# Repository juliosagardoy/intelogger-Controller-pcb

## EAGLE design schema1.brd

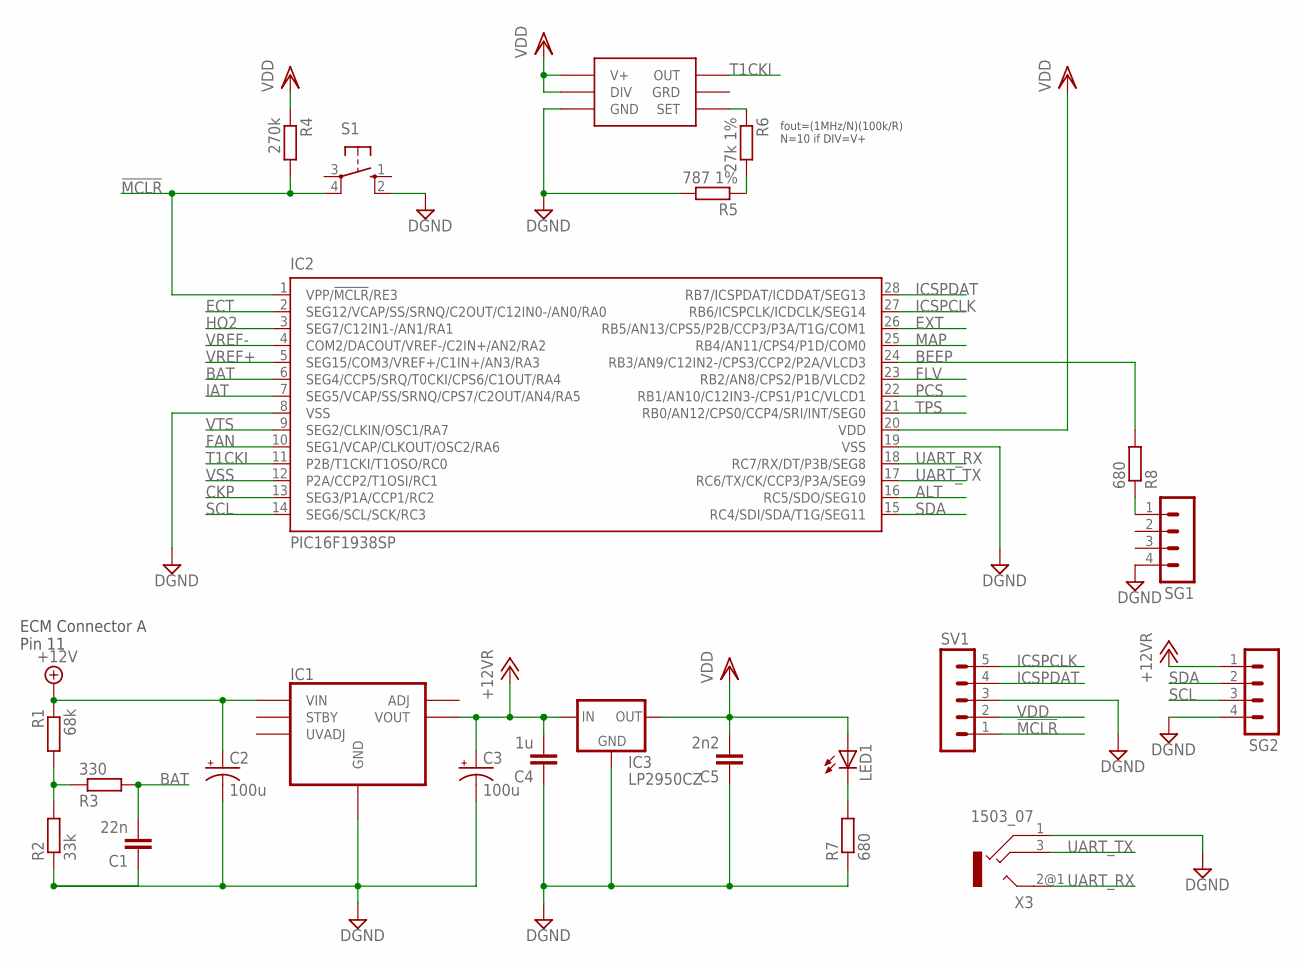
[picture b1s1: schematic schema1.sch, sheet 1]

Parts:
C1: 22n; C5B3
C2, C3: 100u; E5-10,5
C4: 1u; C5B2.5
C5: 2n2; C5B2.5
IC1: EXCALIBURPKG1360; TI_PKG1360
IC2: PIC16F1938SP; DIL28-3
IC3: LP2950CZ; TO92
IC4: LTC6906; TSOT23-6
LED1: LEDCHIP-LED0805; CHIP-LED0805
R1: 68k; M1206
R2: 33k; M1206
R3: 330; M1206
R4: 270k; M1206
R5: 787 1%; M0805
R6: 27k 1%; M0805
R7, R8: 680; M1206
S1: 10-XX; B3F-10XX
SG1, SG2: MA04-1
SV1: MA05-1
X3: 1503_07

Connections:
!MCLR: IC2.1 (VPP/!MCLR!/RE3), R4.2, S1.4 (P1), SV1.1
+12V: C2.+, IC1.P$4 (VIN), IC1.P$5 (VIN), IC1.P$6 (VIN), R1.1; also elsewhere on the board
+12VR: C3.+, C4.2, IC1.P$11 (VOUT), IC1.P$12 (VOUT), IC1.P$13 (VOUT), IC3.3 (IN), SG2.1
ALT: IC2.16 (RC5/SDO/SEG10); also elsewhere on the board
BAT: C1.2, IC2.6 (SEG4/CCP5/SRQ/T0CKI/CPS6/C1OUT/RA4), R3.2
BEEP: IC2.24 (RB3/AN9/C12IN2-/CPS3/CCP2/P2A/VLCD3), R8.2
CKP: IC2.13 (SEG3/P1A/CCP1/RC2); also elsewhere on the board
DGND: C1.1, C2.-, C3.-, C4.1, C5.1, IC1.P$7 (GND), IC1.P$8 (GND), IC1.P$9 (GND), IC1.P$10 (GND), IC2.8 (VSS), IC2.19 (VSS), IC3.2 (GND), IC4.2 (GND), R2.1, R5.2, R7.1, S1.2 (S1), SG1.4, SG2.4, SV1.3, X3.1; also elsewhere on the board
ECT: IC2.2 (SEG12/VCAP/SS/SRNQ/C2OUT/C12IN0-/AN0/RA0); also elsewhere on the board
EXT: IC2.26 (RB5/AN13/CPS5/P2B/CCP3/P3A/T1G/COM1); also elsewhere on the board
FAN: IC2.10 (SEG1/VCAP/CLKOUT/OSC2/RA6); also elsewhere on the board
FLV: IC2.23 (RB2/AN8/CPS2/P1B/VLCD2); also elsewhere on the board
HO2: IC2.3 (SEG7/C12IN1-/AN1/RA1); also elsewhere on the board
IAT: IC2.7 (SEG5/VCAP/SS/SRNQ/CPS7/C2OUT/AN4/RA5); also elsewhere on the board
ICSPCLK: IC2.27 (RB6/ICSPCLK/ICDCLK/SEG14), SV1.5
ICSPDAT: IC2.28 (RB7/ICSPDAT/ICDDAT/SEG13), SV1.4
MAP: IC2.25 (RB4/AN11/CPS4/P1D/COM0); also elsewhere on the board
unnamed: R8.1, SG1.1
unnamed: IC4.4 (SET), R6.1
unnamed: LED1.C, R7.2
unnamed: R5.1, R6.2
unnamed: R1.2, R2.2, R3.1
PCS: IC2.22 (RB1/AN10/C12IN3-/CPS1/P1C/VLCD1); also elsewhere on the board
SCL: IC2.14 (SEG6/SCL/SCK/RC3), SG2.3
SDA: IC2.15 (RC4/SDI/SDA/T1G/SEG11), SG2.2
T1CKI: IC2.11 (P2B/T1CKI/T1OSO/RC0), IC4.1 (OUT)
TPS: IC2.21 (RB0/AN12/CPS0/CCP4/SRI/INT/SEG0); also elsewhere on the board
UART_RX: IC2.18 (RC7/RX/DT/P3B/SEG8), X3.2@1 (2)
UART_TX: IC2.17 (RC6/TX/CK/CCP3/P3A/SEG9), X3.3
VDD: C5.2, IC2.20 (VDD), IC3.1 (OUT), IC4.3 (DIV), IC4.6 (V+), LED1.A, R4.1, SV1.2
VREF+: IC2.5 (SEG15/COM3/VREF+/C1IN+/AN3/RA3); also elsewhere on the board
VREF-: IC2.4 (COM2/DACOUT/VREF-/C2IN+/AN2/RA2); also elsewhere on the board
VSS: IC2.12 (P2A/CCP2/T1OSI/RC1); also elsewhere on the board
VTS: IC2.9 (SEG2/CLKIN/OSC1/RA7); also elsewhere on the board

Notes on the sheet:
ECM Connector A Pin 11
fout=(1MHz/N)(100k/R) N=10 if DIV=V+

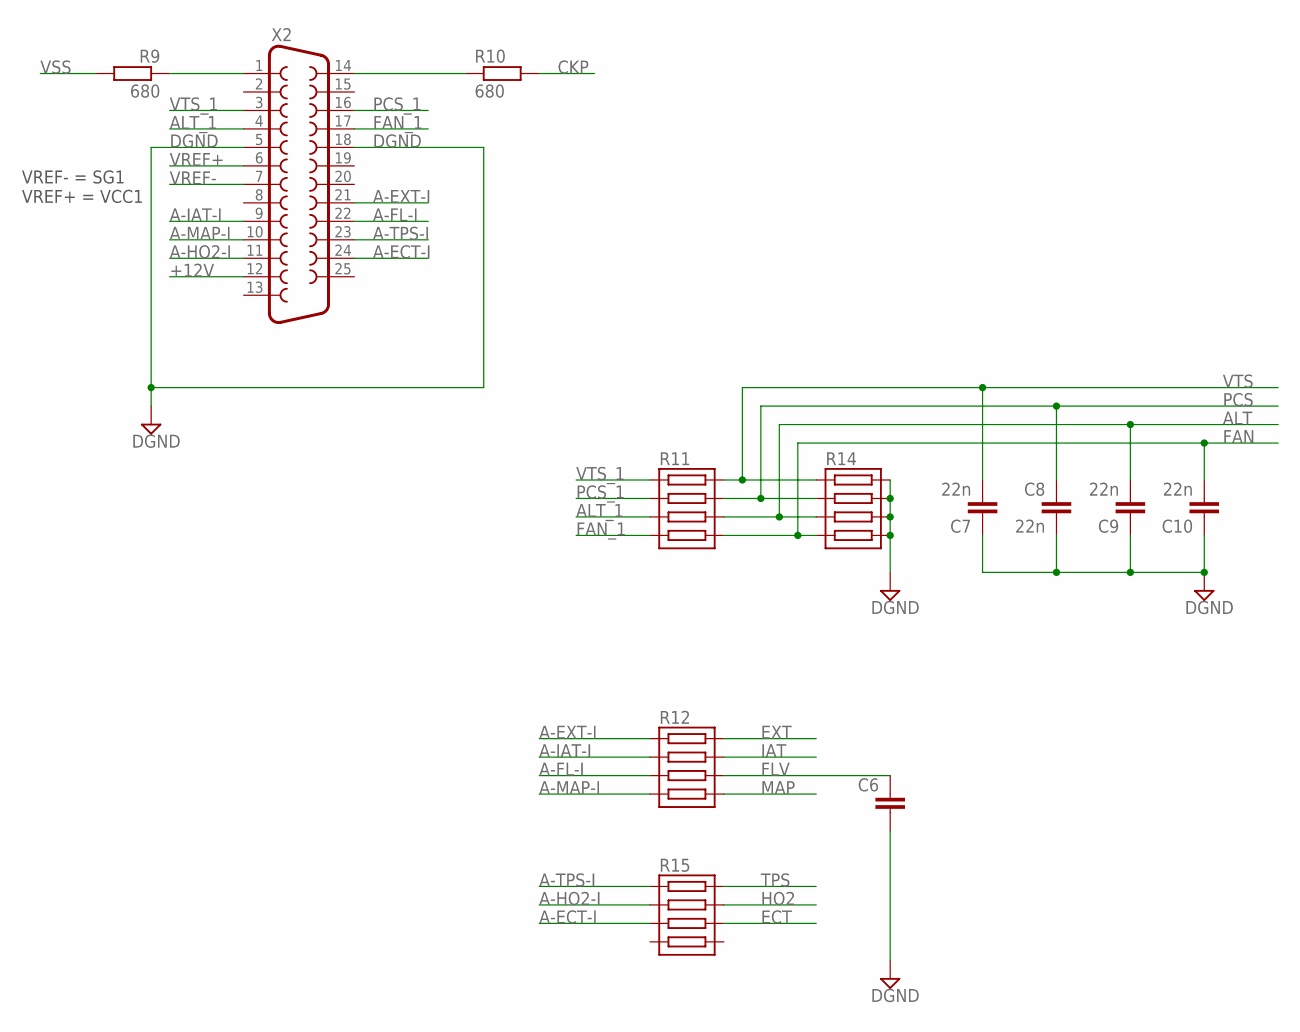
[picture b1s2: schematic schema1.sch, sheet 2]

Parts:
C6: C5/3; C5B3
C7, C8, C9, C10: 22n; C5B3
R9, R10: 680; M1206
R11, R12, R14, R15: RESISTOR_ARRAY; RES_ARRAY_DIP_4
X2: F25H

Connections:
+12V: X2.12; also elsewhere on the board
A-ECT-I: R15.P$5, X2.24
A-EXT-I: R12.P$1, X2.21
A-FL-I: R12.P$5, X2.22
A-HO2-I: R15.P$3, X2.11
A-IAT-I: R12.P$3, X2.9
A-MAP-I: R12.P$7, X2.10
A-TPS-I: R15.P$1, X2.23
ALT: C9.2, R11.P$6, R14.P$5; also elsewhere on the board
ALT_1: R11.P$5, X2.4
CKP: R10.2; also elsewhere on the board
DGND: C6.2, C7.1, C8.2, C9.1, C10.1, R14.P$2, R14.P$4, R14.P$6, R14.P$8, X2.5, X2.18; also elsewhere on the board
ECT: R15.P$6; also elsewhere on the board
EXT: R12.P$2; also elsewhere on the board
FAN: C10.2, R11.P$8, R14.P$7; also elsewhere on the board
FAN_1: R11.P$7, X2.17
FLV: C6.1, R12.P$6; also elsewhere on the board
HO2: R15.P$4; also elsewhere on the board
IAT: R12.P$4; also elsewhere on the board
MAP: R12.P$8; also elsewhere on the board
unnamed: R9.1, X2.1
unnamed: R10.1, X2.14
PCS: C8.1, R11.P$4, R14.P$3; also elsewhere on the board
PCS_1: R11.P$3, X2.16
TPS: R15.P$2; also elsewhere on the board
VREF+: X2.6; also elsewhere on the board
VREF-: X2.7; also elsewhere on the board
VSS: R9.2; also elsewhere on the board
VTS: C7.2, R11.P$2, R14.P$1; also elsewhere on the board
VTS_1: R11.P$1, X2.3

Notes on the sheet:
VREF- = SG1 VREF+ = VCC1

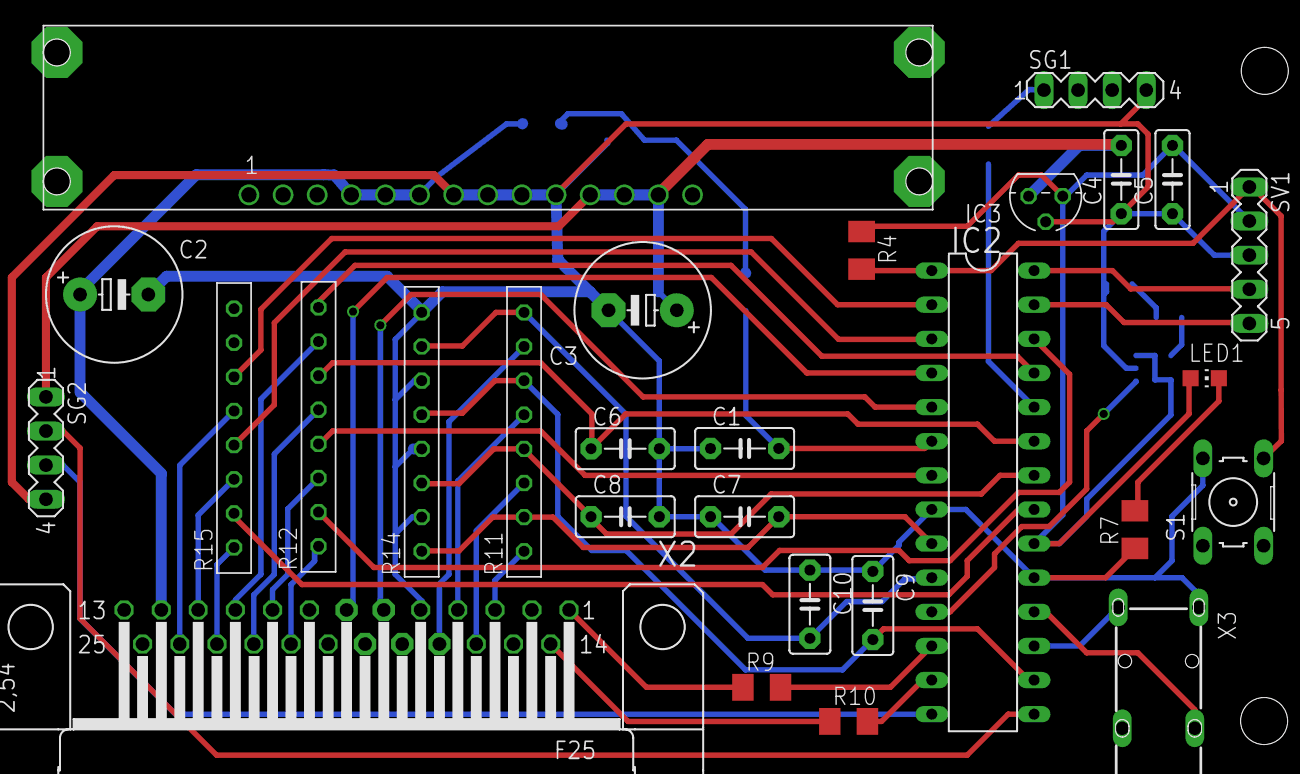
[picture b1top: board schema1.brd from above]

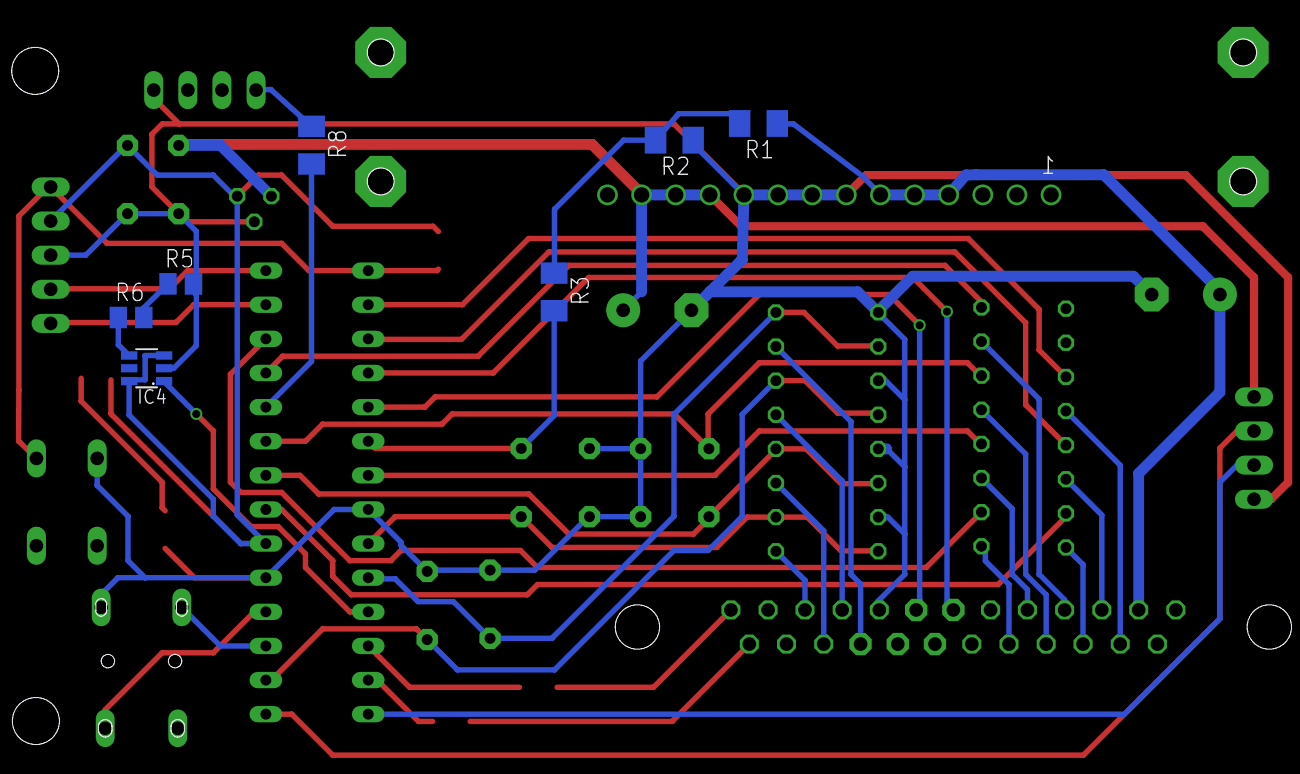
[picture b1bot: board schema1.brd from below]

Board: 4 copper layers, 35 parts (7 on the bottom side), 47 nets.

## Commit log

2016-05-20 Removing eagle epf file
2016-05-20 Schematic with d-sub25 connector and board pcd file
2016-05-25 new file: julio.lbr modified: schema1.brd modified: schema1.sch
2016-05-25 Updated excalibur footprint. Updated board.
2016-06-15 modified: julio.lbr modified: schema1.brd modified: schema1.sch
2016-11-16 adding rev B
